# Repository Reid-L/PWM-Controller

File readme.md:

<h1>PWM Controller</h1>
This project was created in an attempt to use 22V DC LED bars on a 12V DC source.
After locating the MeanWell LDB series of buck boost drivers, I decided I wanted to ad the capability to dim the LEDs, which the driver nicely allowed for. It requires a PWM signal input for dimming.

I decided that the use of a 555 timer was appropriate. I located a circuit that enables dimming from aprox 2%~98%.
The KiCad files are for the 555 timer PWM controller.

The boards are available through OSH Park here: https://oshpark.com/shared_projects/NnH8jZtl

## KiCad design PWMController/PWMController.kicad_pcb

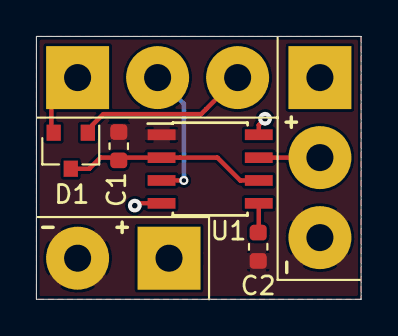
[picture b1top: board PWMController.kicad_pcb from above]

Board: 2 copper layers, 18.0 x 14.6 mm, 7 parts (0 on the bottom side), 8 nets.

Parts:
C1, C2: 1uF; C_0603_1608Metric
D1: MMBD7000LT1G; SOT-23
J1: Conn_01x03; SolderWirePad_1x03_P4.445mm_Drill1.5mm
J2: Conn_01x02; SolderWirePad_1x02_P5.08mm_Drill1.5mm
POT1: 5K; SolderWirePad_1x03_P4.445mm_Drill1.5mm
U1: NE555; SOIC-8_3.9x4.9mm_P1.27mm

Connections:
+12V: J1.1, J2.1, U1.4, U1.8
GND: C1.2, C2.2, J1.3, J2.2, U1.1
unnamed: C1.1, D1.3, U1.2, U1.6
unnamed: C2.1, U1.5
unnamed: D1.1, POT1.3
unnamed: D1.2, POT1.1
unnamed: POT1.2, U1.3
Out: J1.2, U1.7
